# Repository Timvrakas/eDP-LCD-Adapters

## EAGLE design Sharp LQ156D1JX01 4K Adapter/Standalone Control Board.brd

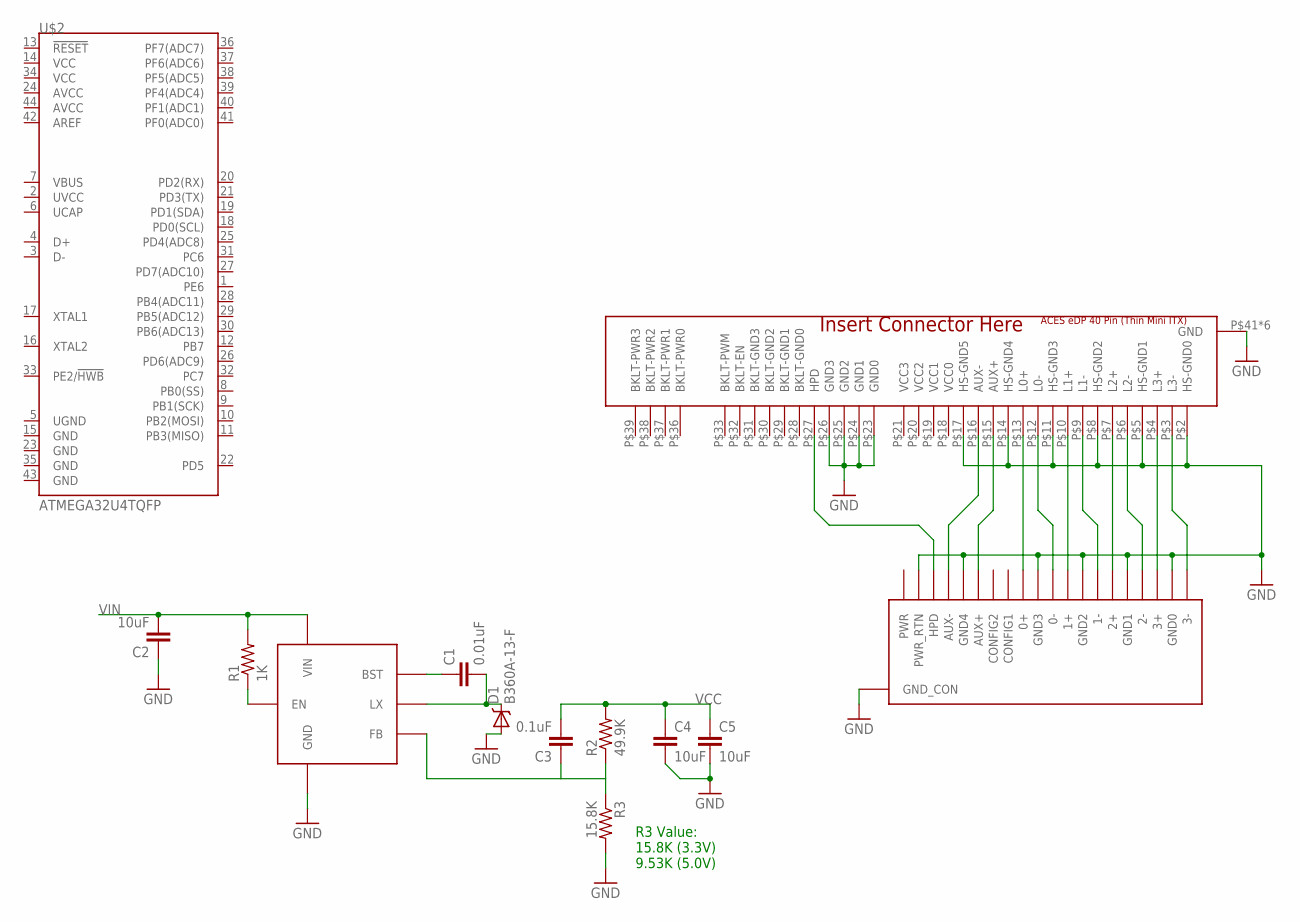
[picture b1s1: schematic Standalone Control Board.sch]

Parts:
C1: 0.01uF; 0805
C2, C4, C5: 10uF; 0805
C3: 0.1uF; 0805
D1: B360A-13-F; SMA-DIODE
F1: EDP-40PIN-ACES; ACES-50203-040
R1: 1K; 0805
R2: 49.9K; 0805
R3: 15.8K; 0805
U$1: DP-SINK; MOLEX-47272-0001
U$2: ATMEGA32U4TQFP; SPARKFUN-DIGITALIC_TQFP44
U$3: AOZ1281-BUCK; 2X2-DFN

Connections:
0_N: F1.P$12 (L0-), U$1.P$14 (0-)
0_P: F1.P$13 (L0+), U$1.P$16 (0+)
1_N: F1.P$9 (L1-), U$1.P$11 (1-)
1_P: F1.P$10 (L1+), U$1.P$13 (1+)
2_N: F1.P$6 (L2-), U$1.P$8 (2-)
2_P: F1.P$7 (L2+), U$1.P$10 (2+)
3_N: F1.P$3 (L3-), U$1.P$5 (3-)
3_P: F1.P$4 (L3+), U$1.P$7 (3+)
AUX_N: F1.P$16 (AUX-), U$1.P$21 (AUX-)
AUX_P: F1.P$15 (AUX+), U$1.P$19 (AUX+)
BKLT-GND0: F1.P$28 (BKLT-GND0)
BKLT-GND1: F1.P$29 (BKLT-GND1)
BKLT-GND2: F1.P$30 (BKLT-GND2)
BKLT-GND3: F1.P$31 (BKLT-GND3)
BKLT-PWR0: F1.P$36 (BKLT-PWR0)
BKLT-PWR1: F1.P$37 (BKLT-PWR1)
BKLT-PWR2: F1.P$38 (BKLT-PWR2)
BKLT-PWR3: F1.P$39 (BKLT-PWR3)
GND: C2.1, C4.2, C5.2, D1.A, F1.P$2 (HS-GND0), F1.P$5 (HS-GND1), F1.P$8 (HS-GND2), F1.P$11 (HS-GND3), F1.P$14 (HS-GND4), F1.P$17 (HS-GND5), F1.P$23 (GND0), F1.P$24 (GND1), F1.P$25 (GND2), F1.P$26 (GND3), F1.P$41 (GND), F1.P$42 (GND), F1.P$43 (GND), F1.P$44 (GND), F1.P$45 (GND), F1.P$46 (GND), R3.2, U$1.GND1 (GND_CON), U$1.GND2 (GND_CON), U$1.GND3 (GND_CON), U$1.GND4 (GND_CON), U$1.P$6 (GND0), U$1.P$9 (GND1), U$1.P$12 (GND2), U$1.P$15 (GND3), U$1.P$20 (GND4), U$1.P$23 (PWR_RTN), U$3.6 (GND), U$3.7 (GND), U$3.CENTER (GND)
unnamed: R1.1, U$3.4 (EN)
unnamed: C3.1, U$3.5 (FB)
unnamed: C1.1, U$3.8 (BST)
unnamed: C1.2, D1.C, U$3.1 (LX)
unnamed: R2.1, R3.1
unnamed: F1.P$27 (HPD), U$1.P$22 (HPD)
PWR: U$1.P$24 (PWR)
VCC: C3.2, C4.1, C5.1, R2.2
VCC0: F1.P$18 (VCC0)
VCC1: F1.P$19 (VCC1)
VCC2: F1.P$20 (VCC2)
VCC3: F1.P$21 (VCC3)
VIN: C2.2, R1.2, U$3.2 (VIN), U$3.3 (VIN)

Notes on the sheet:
R3 Value: 15.8K (3.3V) 9.53K (5.0V)

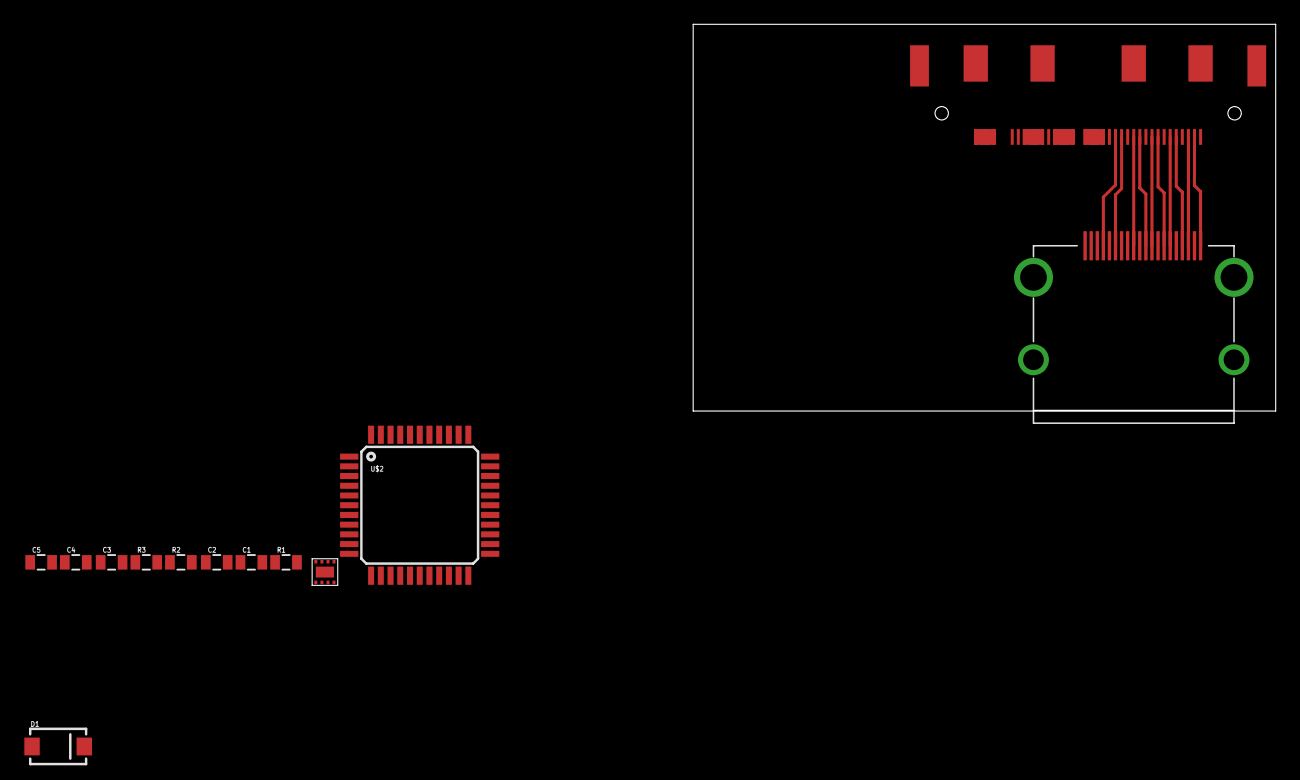
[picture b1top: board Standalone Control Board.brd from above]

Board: 2 copper layers, 47.9 x 31.8 mm, 13 parts (0 on the bottom side), 19 nets.

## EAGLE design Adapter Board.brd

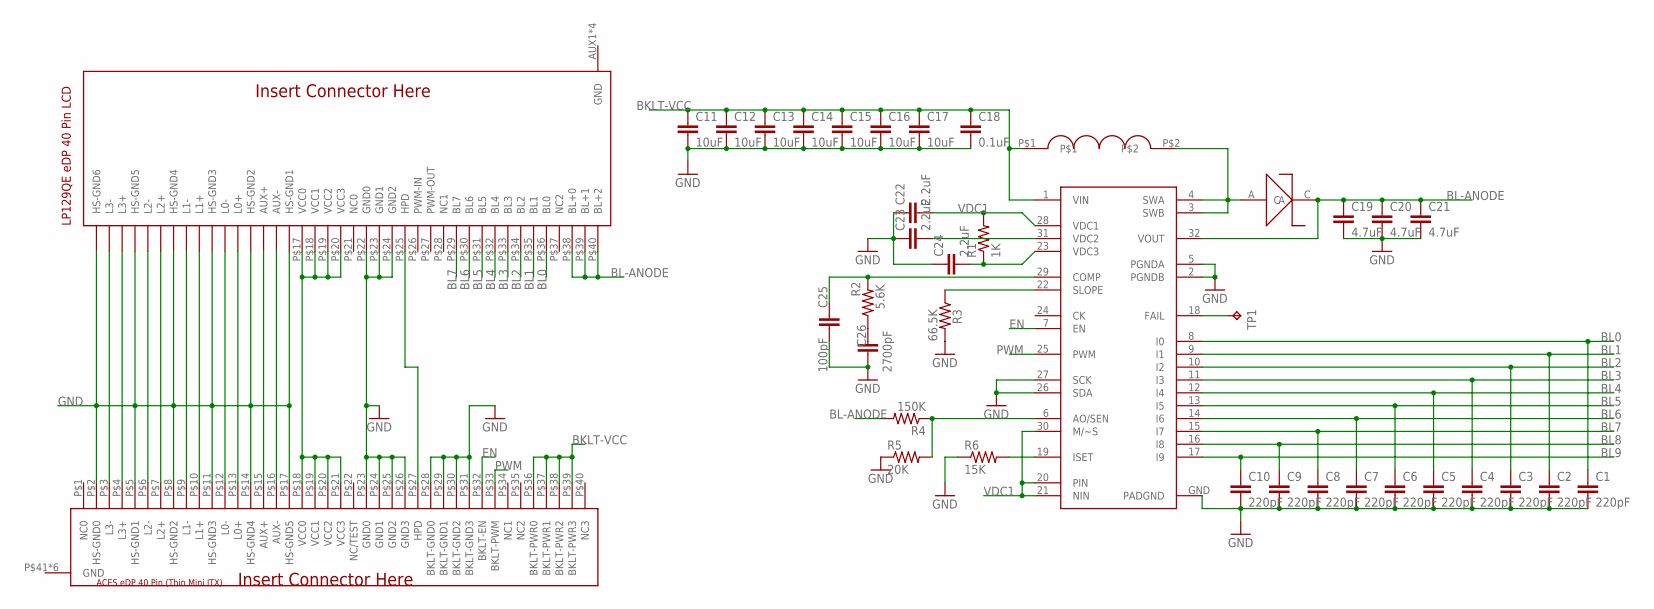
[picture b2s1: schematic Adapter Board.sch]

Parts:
C1, C2, C3, C4, C5, C6, C7, C8, C9, C10: 220pF; 0805
C11, C12, C13, C14, C15, C16, C17: 10uF; 1206
C18: 0.1uF; 0805
C19, C20, C21: 4.7uF; 0805
C22, C23, C24: 2.2uF; 0805
C25: 100pF; 0805
C26: 2700pF; 0805
DIOD-S: SK38A-DIODE
R1: 1K; 0805
R2: 5.6K; 0805
R3: 66.5K; 0805
R4: 150K; 0805
R5: 20K; 0805
R6: 15K; 0805
TP1: TPTP15R; TP15R
U$1: EDP-40PIN-ACES; ACES-50203-040
U$2: LP129QE-EDP-40; I-PEX-20474-040E-12
U$3: MC34844-LED-DRIVER; QFN32
U$4: ASPI-8040S-INCUCTOR; INDUCTOR

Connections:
BKLT-VCC: C11.1, C12.1, C13.1, C14.1, C15.1, C16.1, C17.1, C18.1, U$1.P$36 (BKLT-PWR0), U$1.P$37 (BKLT-PWR1), U$1.P$38 (BKLT-PWR2), U$1.P$39 (BKLT-PWR3), U$3.1 (VIN), U$4.P$1
BL0: C1.1, U$2.P$36 (BL0), U$3.8 (I0)
BL1: C2.1, U$2.P$35 (BL1), U$3.9 (I1)
BL2: C3.1, U$2.P$34 (BL2), U$3.10 (I2)
BL3: C4.1, U$2.P$33 (BL3), U$3.11 (I3)
BL4: C5.1, U$2.P$32 (BL4), U$3.12 (I4)
BL5: C6.1, U$2.P$31 (BL5), U$3.13 (I5)
BL6: C7.1, U$2.P$30 (BL6), U$3.14 (I6)
BL7: C8.1, U$2.P$29 (BL7), U$3.15 (I7)
BL8: C9.1, U$3.16 (I8)
BL9: C10.1, U$3.17 (I9)
BL-ANODE: C19.1, C20.1, C21.1, DIOD-S.C, R4.2, U$2.P$38 (BL+0), U$2.P$39 (BL+1), U$2.P$40 (BL+2), U$3.32 (VOUT)
EN: U$1.P$32 (BKLT-EN), U$3.7 (EN)
GND: C1.2, C2.2, C3.2, C4.2, C5.2, C6.2, C7.2, C8.2, C9.2, C10.2, C11.2, C12.2, C13.2, C14.2, C15.2, C16.2, C17.2, C18.2, C19.2, C20.2, C21.2, C22.1, C23.1, C24.1, C25.2, C26.2, R3.2, R5.1, R6.1, U$1.P$2 (HS-GND0), U$1.P$5 (HS-GND1), U$1.P$8 (HS-GND2), U$1.P$11 (HS-GND3), U$1.P$14 (HS-GND4), U$1.P$17 (HS-GND5), U$1.P$23 (GND0), U$1.P$24 (GND1), U$1.P$25 (GND2), U$1.P$26 (GND3), U$1.P$28 (BKLT-GND0), U$1.P$29 (BKLT-GND1), U$1.P$30 (BKLT-GND2), U$1.P$31 (BKLT-GND3), U$1.P$41 (GND), U$1.P$42 (GND), U$1.P$43 (GND), U$1.P$44 (GND), U$1.P$45 (GND), U$1.P$46 (GND), U$2.AUX1 (GND), U$2.AUX2 (GND), U$2.GND-PAD1 (GND), U$2.GND-PAD2 (GND), U$2.P$1 (HS-GND6), U$2.P$4 (HS-GND5), U$2.P$7 (HS-GND4), U$2.P$10 (HS-GND3), U$2.P$13 (HS-GND2), U$2.P$16 (HS-GND1), U$2.P$22 (GND0), U$2.P$23 (GND1), U$2.P$24 (GND2), U$3.2 (PGNDB), U$3.5 (PGNDA), U$3.26 (SDA), U$3.27 (SCK), U$3.GND
HPD: U$1.P$27 (HPD), U$2.P$25 (HPD)
unnamed: C25.1, R2.2, U$3.29 (COMP)
unnamed: U$1.P$3 (L3-), U$2.P$2 (L3-)
unnamed: U$1.P$4 (L3+), U$2.P$3 (L3+)
unnamed: C23.2, U$3.31 (VDC2)
unnamed: U$1.P$6 (L2-), U$2.P$5 (L2-)
unnamed: U$1.P$7 (L2+), U$2.P$6 (L2+)
unnamed: U$1.P$9 (L1-), U$2.P$8 (L1-)
unnamed: U$1.P$10 (L1+), U$2.P$9 (L1+)
unnamed: C24.2, R1.1, U$3.23 (VDC3)
unnamed: U$1.P$12 (L0-), U$2.P$11 (L0-)
unnamed: U$1.P$13 (L0+), U$2.P$12 (L0+)
unnamed: C26.1, R2.1
unnamed: U$1.P$15 (AUX+), U$2.P$14 (AUX+)
unnamed: U$1.P$16 (AUX-), U$2.P$15 (AUX-)
unnamed: R4.1, R5.2, U$3.6 (AO/SEN)
unnamed: R3.1, U$3.22 (SLOPE)
unnamed: TP1.TP, U$3.18 (FAIL)
unnamed: R6.2, U$3.19 (ISET)
PNL-VCC: U$1.P$18 (VCC0), U$1.P$19 (VCC1), U$1.P$20 (VCC2), U$1.P$21 (VCC3), U$2.P$17 (VCC0), U$2.P$18 (VCC1), U$2.P$19 (VCC2), U$2.P$20 (VCC3)
PWM: U$1.P$33 (BKLT-PWM), U$3.25 (PWM)
SWA/B: DIOD-S.A, U$3.3 (SWB), U$3.4 (SWA), U$4.P$2
VDC1: C22.2, R1.2, U$3.20 (PIN), U$3.21 (NIN), U$3.28 (VDC1), U$3.30 (M/~S)

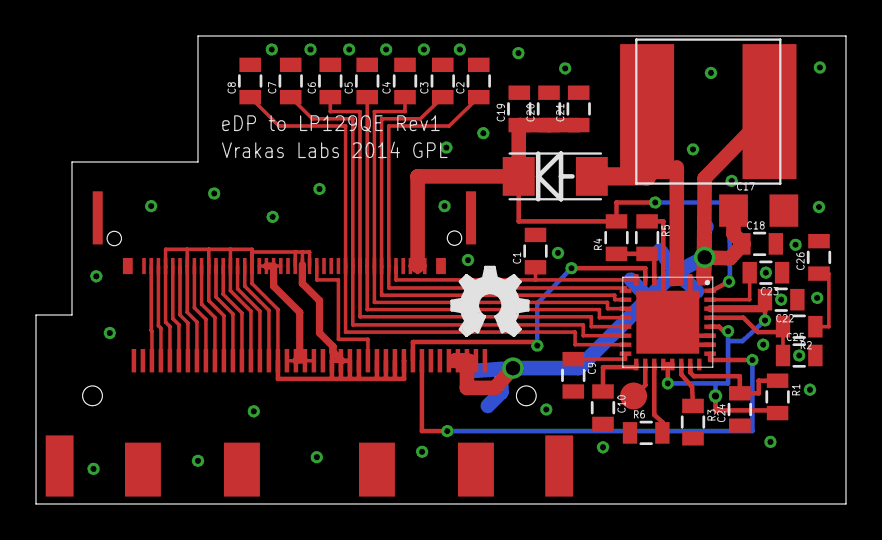
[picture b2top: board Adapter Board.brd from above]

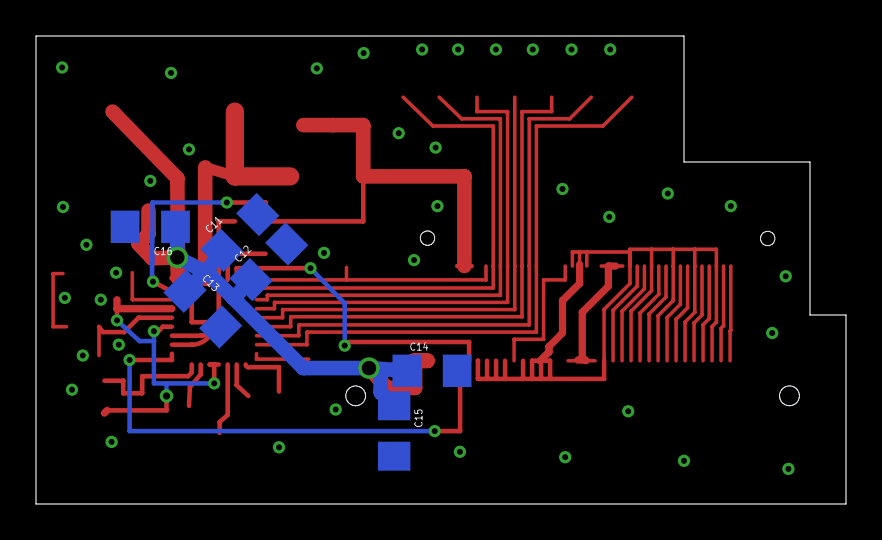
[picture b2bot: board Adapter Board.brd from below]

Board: 2 copper layers, 45.0 x 26.0 mm, 39 parts (6 on the bottom side), 37 nets.

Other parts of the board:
U$5: OSHW_FILLX150_NOTEXT

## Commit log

2014-09-02 Initial Rev1 Commit
    First revision boards
2014-09-02 Re-arangement
2014-12-12 Rev.2 Commit
    Joined common pads, removed orphaned pads, aligned passive 0805s. More
    room to solder QFN. Full rectangular board.
2015-02-28 This repo is now for more than just the original Adapter board. Reogranized the folder structure for better eagle integration.
2015-02-28 setup .gitignore
    used github/gitignore EAGLE defaults
2015-03-01 Working on sharp 4k. so many k's

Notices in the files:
Adapter Board.brd:
Vrakas Labs 2014 GPL
parts and their libraries:
SparkFun-Passives: Licensing: CC v3.0 Share-Alike You are welcome to use this library for commercial purposes.
